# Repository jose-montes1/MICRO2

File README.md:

# MICRO2
Repository for my embedded design class

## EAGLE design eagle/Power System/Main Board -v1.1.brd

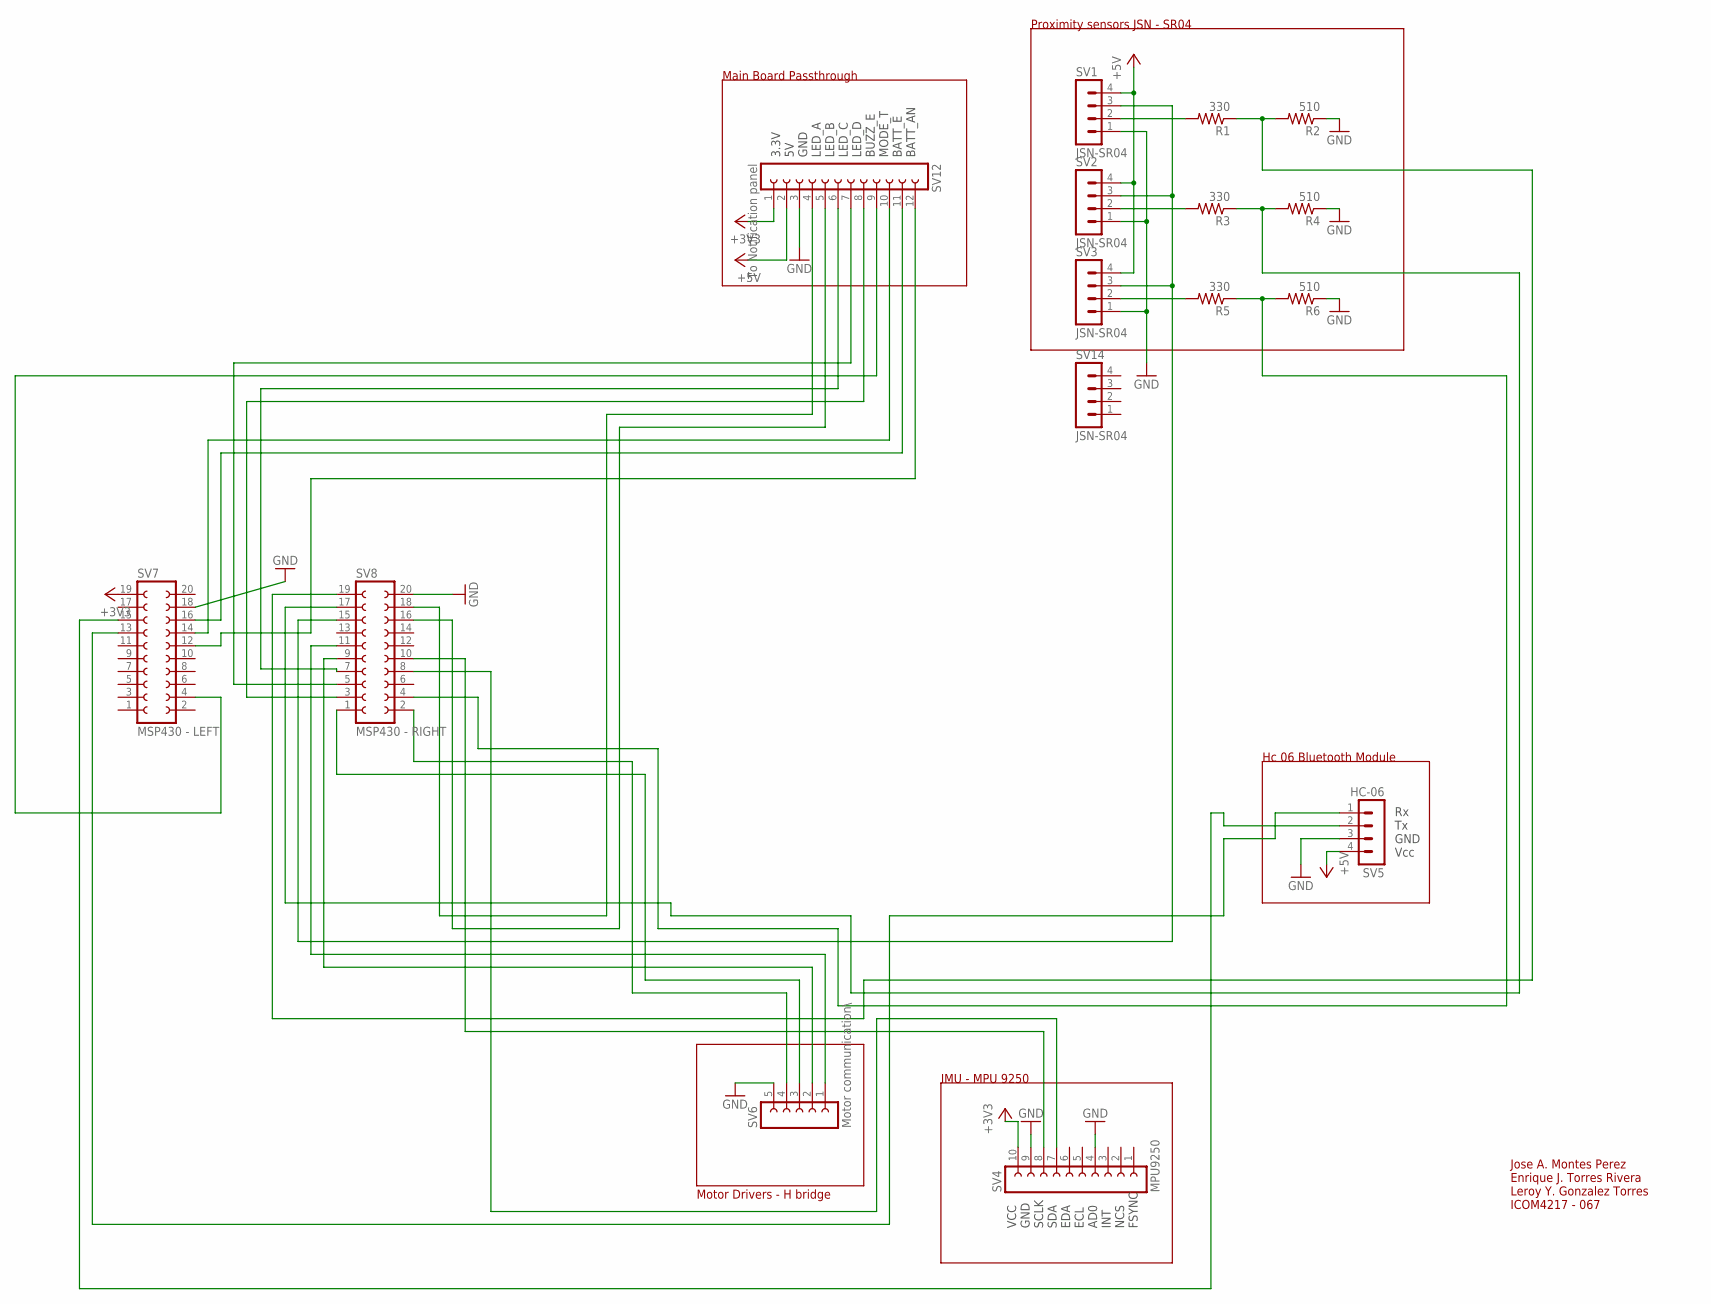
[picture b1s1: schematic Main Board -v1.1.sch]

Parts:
R1, R3, R5: 330; 0207/10
R2, R4, R6: 510; 0207/10
SV1, SV2, SV3, SV14: JSN-SR04; MA04-1
SV4: MPU9250; FE10
SV5: HC-06; MA04-1
SV6: Motor communication\; FE05-1
SV7: MSP430 - LEFT; FE10-2
SV8: MSP430 - RIGHT; FE10-2
SV12: To Notification panel; FE12

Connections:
+3V3: SV4.10, SV7.19, SV12.1
+5V: SV1.4, SV2.4, SV3.4, SV5.4, SV12.2
GND: R2.1, R4.1, R6.1, SV1.1, SV2.1, SV3.1, SV4.4, SV4.9, SV5.3, SV6.5, SV7.18, SV8.20, SV12.3
unnamed: R1.2, SV1.2
unnamed: SV7.12, SV12.12
unnamed: SV4.8, SV8.10
unnamed: R1.1, R2.2, SV8.19
unnamed: SV6.4, SV8.2
unnamed: R3.2, SV2.2
unnamed: SV6.3, SV8.1
unnamed: SV7.14, SV12.10
unnamed: SV6.2, SV8.9
unnamed: SV6.1, SV8.11
unnamed: R3.1, R4.2, SV8.17
unnamed: SV7.16, SV12.11
unnamed: SV4.7, SV8.8
unnamed: SV5.1, SV7.13
unnamed: R5.2, SV3.2
unnamed: SV8.16, SV12.5
unnamed: R5.1, R6.2, SV8.4
unnamed: SV8.18, SV12.4
unnamed: SV1.3, SV2.3, SV3.3, SV8.15
unnamed: SV8.3, SV12.8
unnamed: SV5.2, SV7.15
unnamed: SV8.5, SV12.7
unnamed: SV8.7, SV12.6
unnamed: SV7.4, SV12.9

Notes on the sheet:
Proximity sensors JSN - SR04
VCC GND SCLK SDA EDA ECL AD0 INT NCS FSYNC
IMU - MPU 9250
Motor Drivers - H bridge
Hc 06 Bluetooth Module
Rx Tx GND Vcc
Jose A. Montes Perez Enrique J. Torres Rivera Leroy Y. Gonzalez Torres ICOM4217 - 067
Main Board Passthrough
3.3V 5V GND LED_A LED_B LED_C LED_D BUZZ_E MODE_T BATT_E BATT_AN

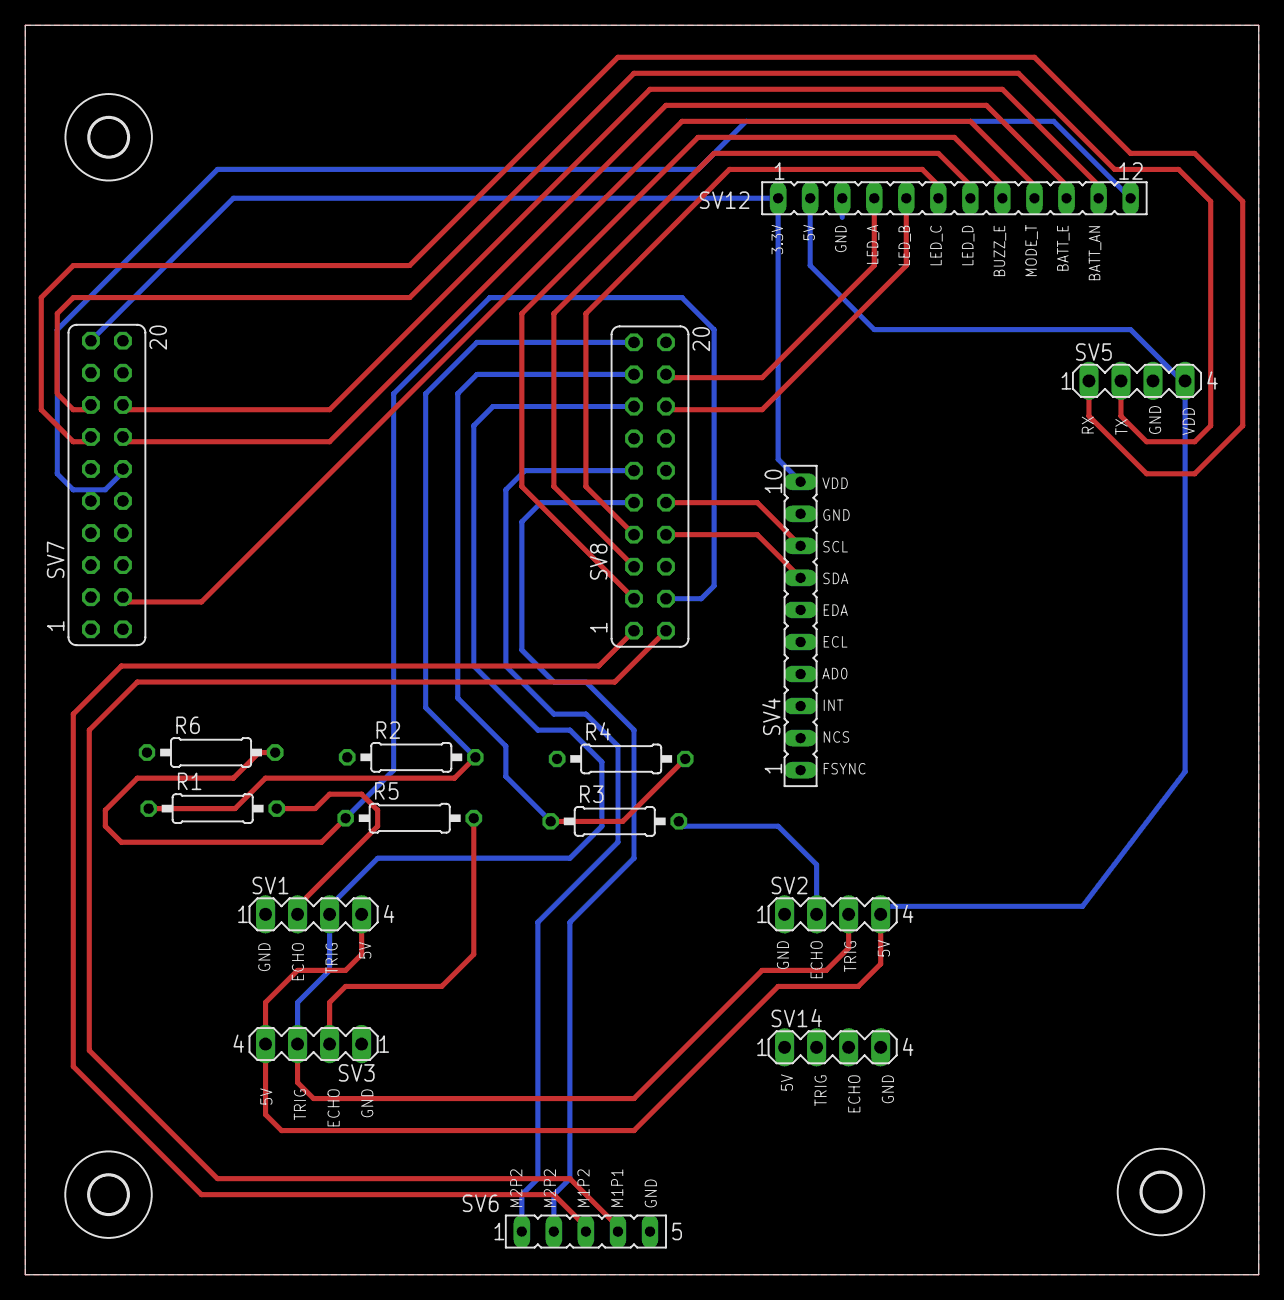
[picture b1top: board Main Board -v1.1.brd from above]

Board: 2 copper layers, 97.8 x 99.1 mm, 19 parts (0 on the bottom side), 27 nets.

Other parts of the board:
U$1, U$2, U$3: 3,0

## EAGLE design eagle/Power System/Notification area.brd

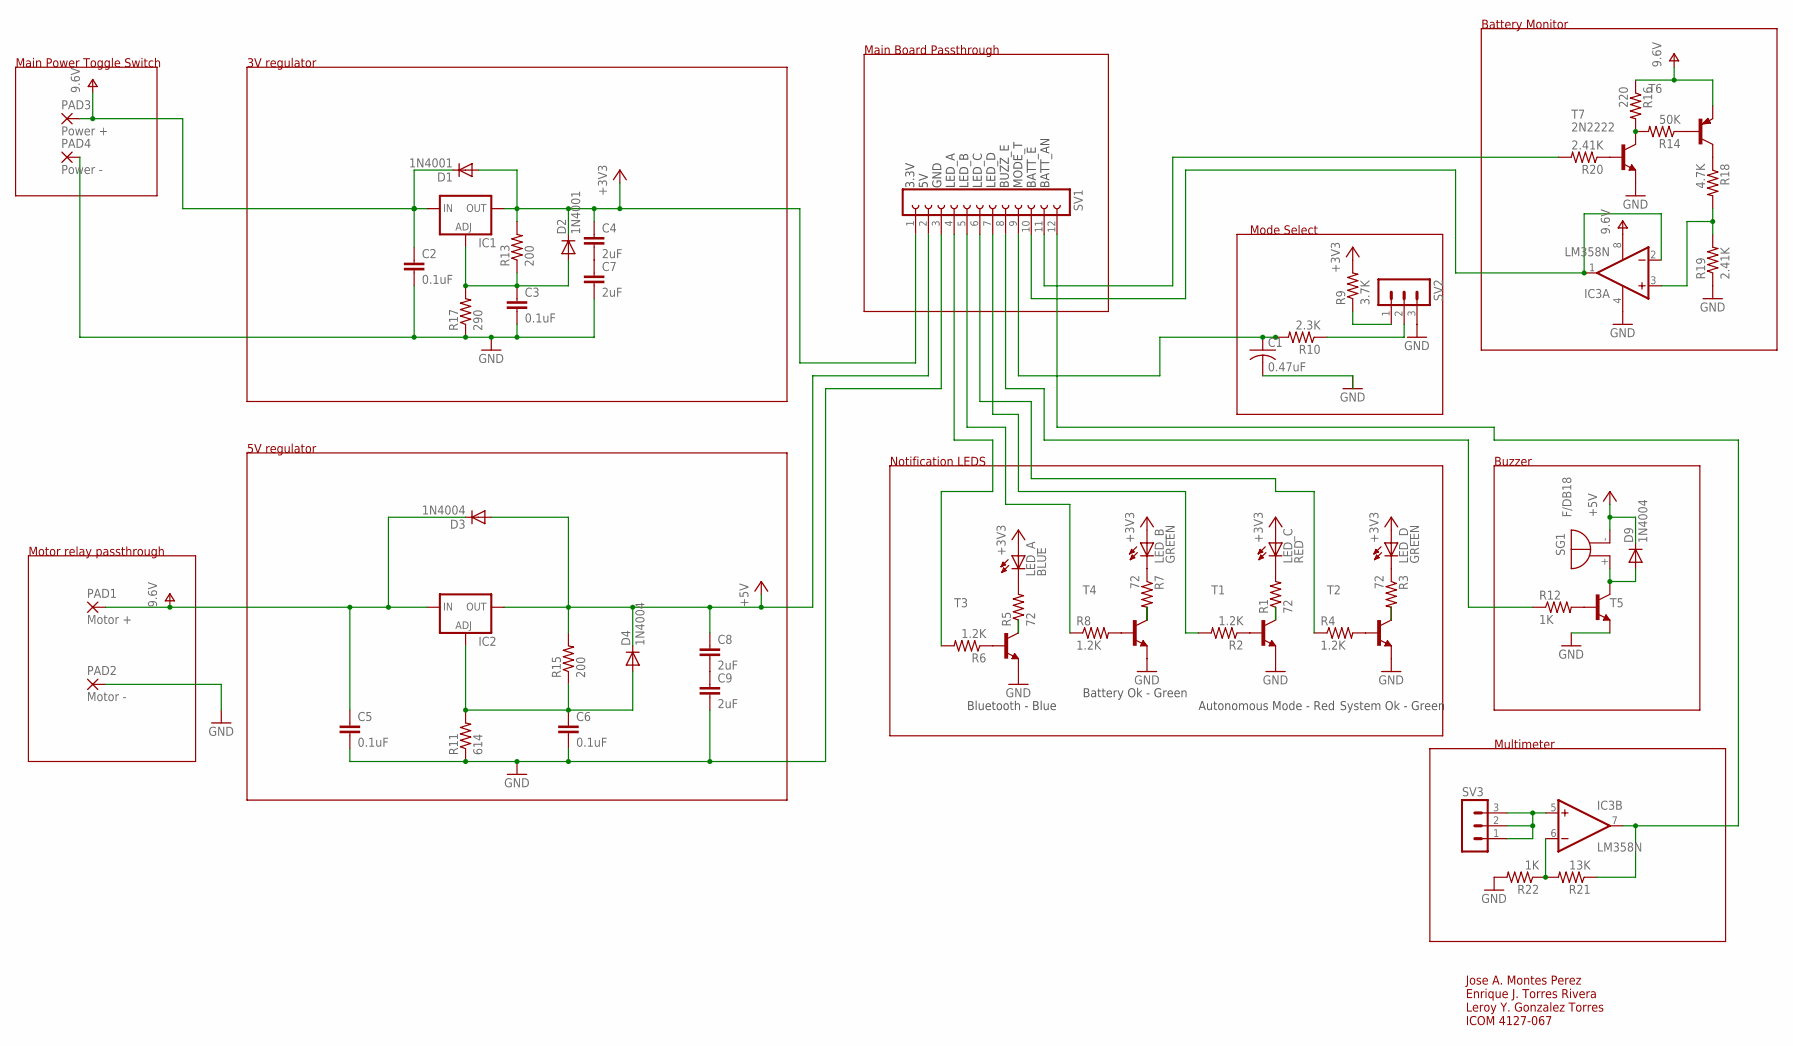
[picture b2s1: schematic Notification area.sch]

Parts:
C1: 0.47uF; C025-030X050
C2, C3, C5, C6: 0.1uF; C2.5-3
C4, C7, C8, C9: 2uF; C2.5-3
D1, D2: 1N4001; DO41-10
D3, D4, D9: 1N4004; DO41-10
IC1, IC2: LM317TS; 317TS
IC3: LM358N; DIL08
LED_A: BLUE; HLMP6
LED_B: GREEN; HLMP6
LED_C: RED; HLMP6
LED_D: GREEN; HLMP6
PAD1: Motor +; 5-2,5
PAD2: Motor -; 5-2,5
PAD3: Power +; 5-2,5
PAD4: Power -; 5-2,5
R1, R3, R5, R7: 72; 0204/7
R2, R4, R6, R8: 1.2K; 0204/7
R9: 3.7K; 0204/7
R10: 2.3K; 0204/7
R11: 614; 0204/7
R12: 1K; 0207/7
R13, R15: 200; 0204/7
R14: 50K; 0204/7
R16: 220; 0204/7
R17: 290; 0204/7
R18: 4.7K; 0204/7
R19, R20: 2.41K; 0204/7
R21: 13K; 0204/7
R22: 1K; 0204/7
SG1: F/DB18
SV1: FE12-1; FE12
SV2, SV3: MA03-1
T1, T2, T3, T4, T5: 2N2222-NPN-TO92-EBC; TO92-EBC
T6: 2N3906-PNP-TO92-EBC; TO92-EBC
T7: 2N2222; TO18

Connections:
+3V3: C4.1, D1.A, D2.C, IC1.2 (OUT), LED_A.A, LED_B.A, LED_C.A, LED_D.A, R9.2, R13.2, SV1.1
+5V: C8.1, D3.A, D4.C, D9.C, IC2.2 (OUT), R15.2, SG1.-, SV1.2
GND: C1.2, C2.2, C3.2, C5.2, C6.2, C7.2, C9.2, IC3.4 (V-), PAD2.1, PAD4.1, R11.1, R17.1, R19.1, R22.2, SV1.3, SV2.3, T1.E, T2.E, T3.E, T4.E, T5.E, T7.1 (E)
unnamed: LED_C.K, R1.2
unnamed: R2.1, T1.B
unnamed: LED_D.K, R3.1
unnamed: R4.2, T2.B
unnamed: LED_A.K, R5.2
unnamed: R6.1, T3.B
unnamed: LED_B.K, R7.1
unnamed: R8.2, T4.B
unnamed: R6.2, SV1.4
unnamed: C1.1, R10.2, SV1.9
unnamed: R8.1, SV1.5
unnamed: R4.1, SV1.6
unnamed: R9.1, SV2.1
unnamed: R5.1, T3.C
unnamed: R12.2, T5.B
unnamed: C4.2, C7.1
unnamed: R2.2, SV1.7
unnamed: C3.1, D2.A, IC1.1 (ADJ), R13.1, R17.2
unnamed: C6.1, D4.A, IC2.1 (ADJ), R11.2, R15.1
unnamed: D9.A, SG1.+, T5.C
unnamed: R14.1, T6.B
unnamed: R14.2, R16.2, T7.3 (C)
unnamed: R12.1, SV1.8
unnamed: R18.1, T6.C
unnamed: R20.2, SV1.11
unnamed: IC3.3 (+IN), R18.2, R19.2
unnamed: R20.1, T7.2 (B)
unnamed: C8.2, C9.1
unnamed: R7.2, T4.C
unnamed: R1.1, T1.C
unnamed: R3.2, T2.C
unnamed: R10.1, SV2.2
unnamed: IC3.6 (-IN), R21.2, R22.1
unnamed: IC3.7 (OUT), R21.1, SV1.12
unnamed: IC3.5 (+IN), SV3.1, SV3.2, SV3.3
unnamed: IC3.1 (OUT), IC3.2 (-IN), SV1.10
V+: C2.1, C5.1, D1.C, D3.C, IC1.3 (IN), IC2.3 (IN), IC3.8 (V+), PAD1.1, PAD3.1, R16.1, T6.E

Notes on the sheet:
Main Board Passthrough
Notification LEDS
3.3V 5V GND LED_A LED_B LED_C LED_D BUZZ_E MODE_T BATT_E BATT_AN
Jose A. Montes Perez Enrique J. Torres Rivera Leroy Y. Gonzalez Torres ICOM 4127-067
Mode Select
5V regulator
3V regulator
Buzzer
Main Power Toggle Switch
Motor relay passthrough
Battery Monitor
Bluetooth - Blue
Battery Ok - Green
Autonomous Mode - Red
System Ok - Green
Multimeter

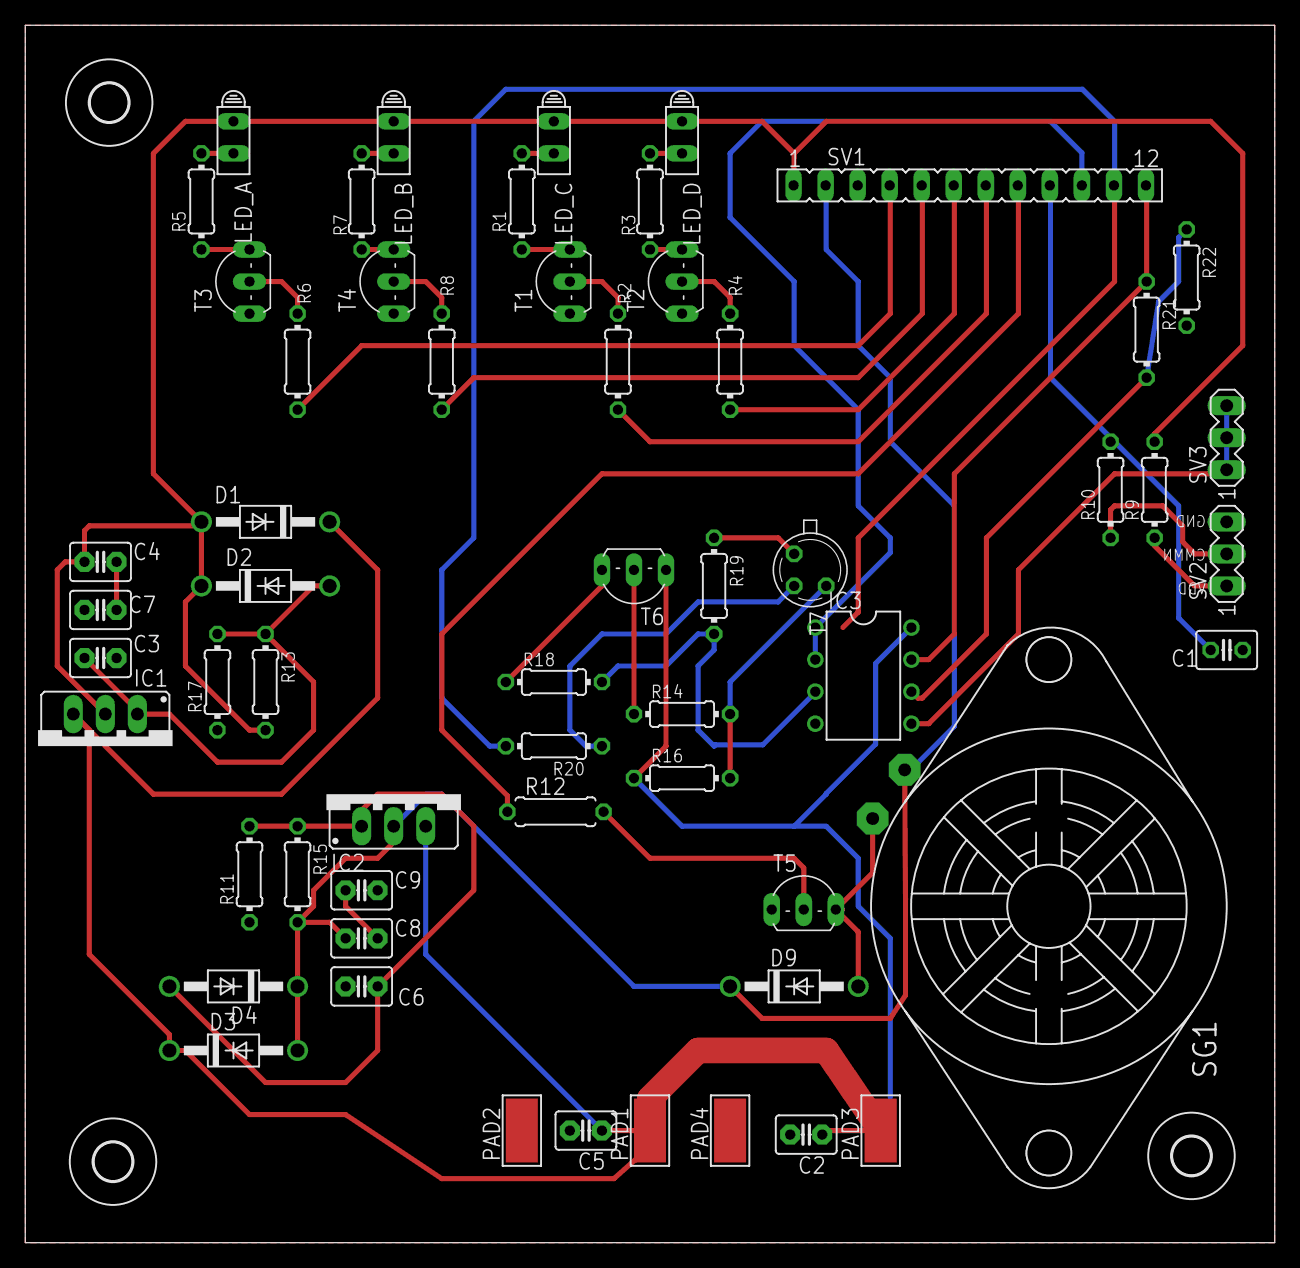
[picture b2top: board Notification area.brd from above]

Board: 2 copper layers, 99.1 x 96.5 mm, 61 parts (0 on the bottom side), 40 nets.

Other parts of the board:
U$1, U$2, U$4: 3,0

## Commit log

2016-10-25 On branch master Your branch is up-to-date with 'origin/master'.
    Changes to be committed:
    new file: MPU6050 Drivers/.ccsproject
    new file: MPU6050 Drivers/.cproject
    new file: MPU6050 Drivers/.project
    new file: MPU6050 Drivers/.settings/org.eclipse.cdt.codan.core.prefs
    new file: MPU6050 Drivers/.settings/org.eclipse.cdt.debug.core.prefs
2016-10-25 Minor update to Serial_JMP
2016-10-25 Serial lightly modified, Added General
2016-10-25 Small serial update
2016-10-26 Big update: UART Working, I2C testing
2016-10-26 BluetoothModule
2016-10-26 Revert "BluetoothModule"
    This reverts commit cf7f597db166418f05405976c8ffd40fdfd8e99c.
2016-10-26 BluetoothModuleV1
2016-10-26 Removed Debugging Indicators
2016-10-26 Added servo pwm library, tested mpu
2016-10-27 Finished main with serial, no testing
2016-10-27 Changes to be committed: modified: MPU6050 Drivers/.project
2016-10-31 Motor drive test
2016-11-06 Eagle libs and DMP files
2016-11-07 PCB layout beta
2016-11-09 Redid Serial JMP in MPU6050 update
2016-11-09 Redid Serial JMP in MPU6050 update in latest drivers
2016-11-11 updated pcb
2016-11-12 resized main board
2016-11-13 final pcb versions
2016-11-13 final final pcb
2016-11-14 final final final eagle files
2016-11-14 added multimeter
2016-12-03 last push
